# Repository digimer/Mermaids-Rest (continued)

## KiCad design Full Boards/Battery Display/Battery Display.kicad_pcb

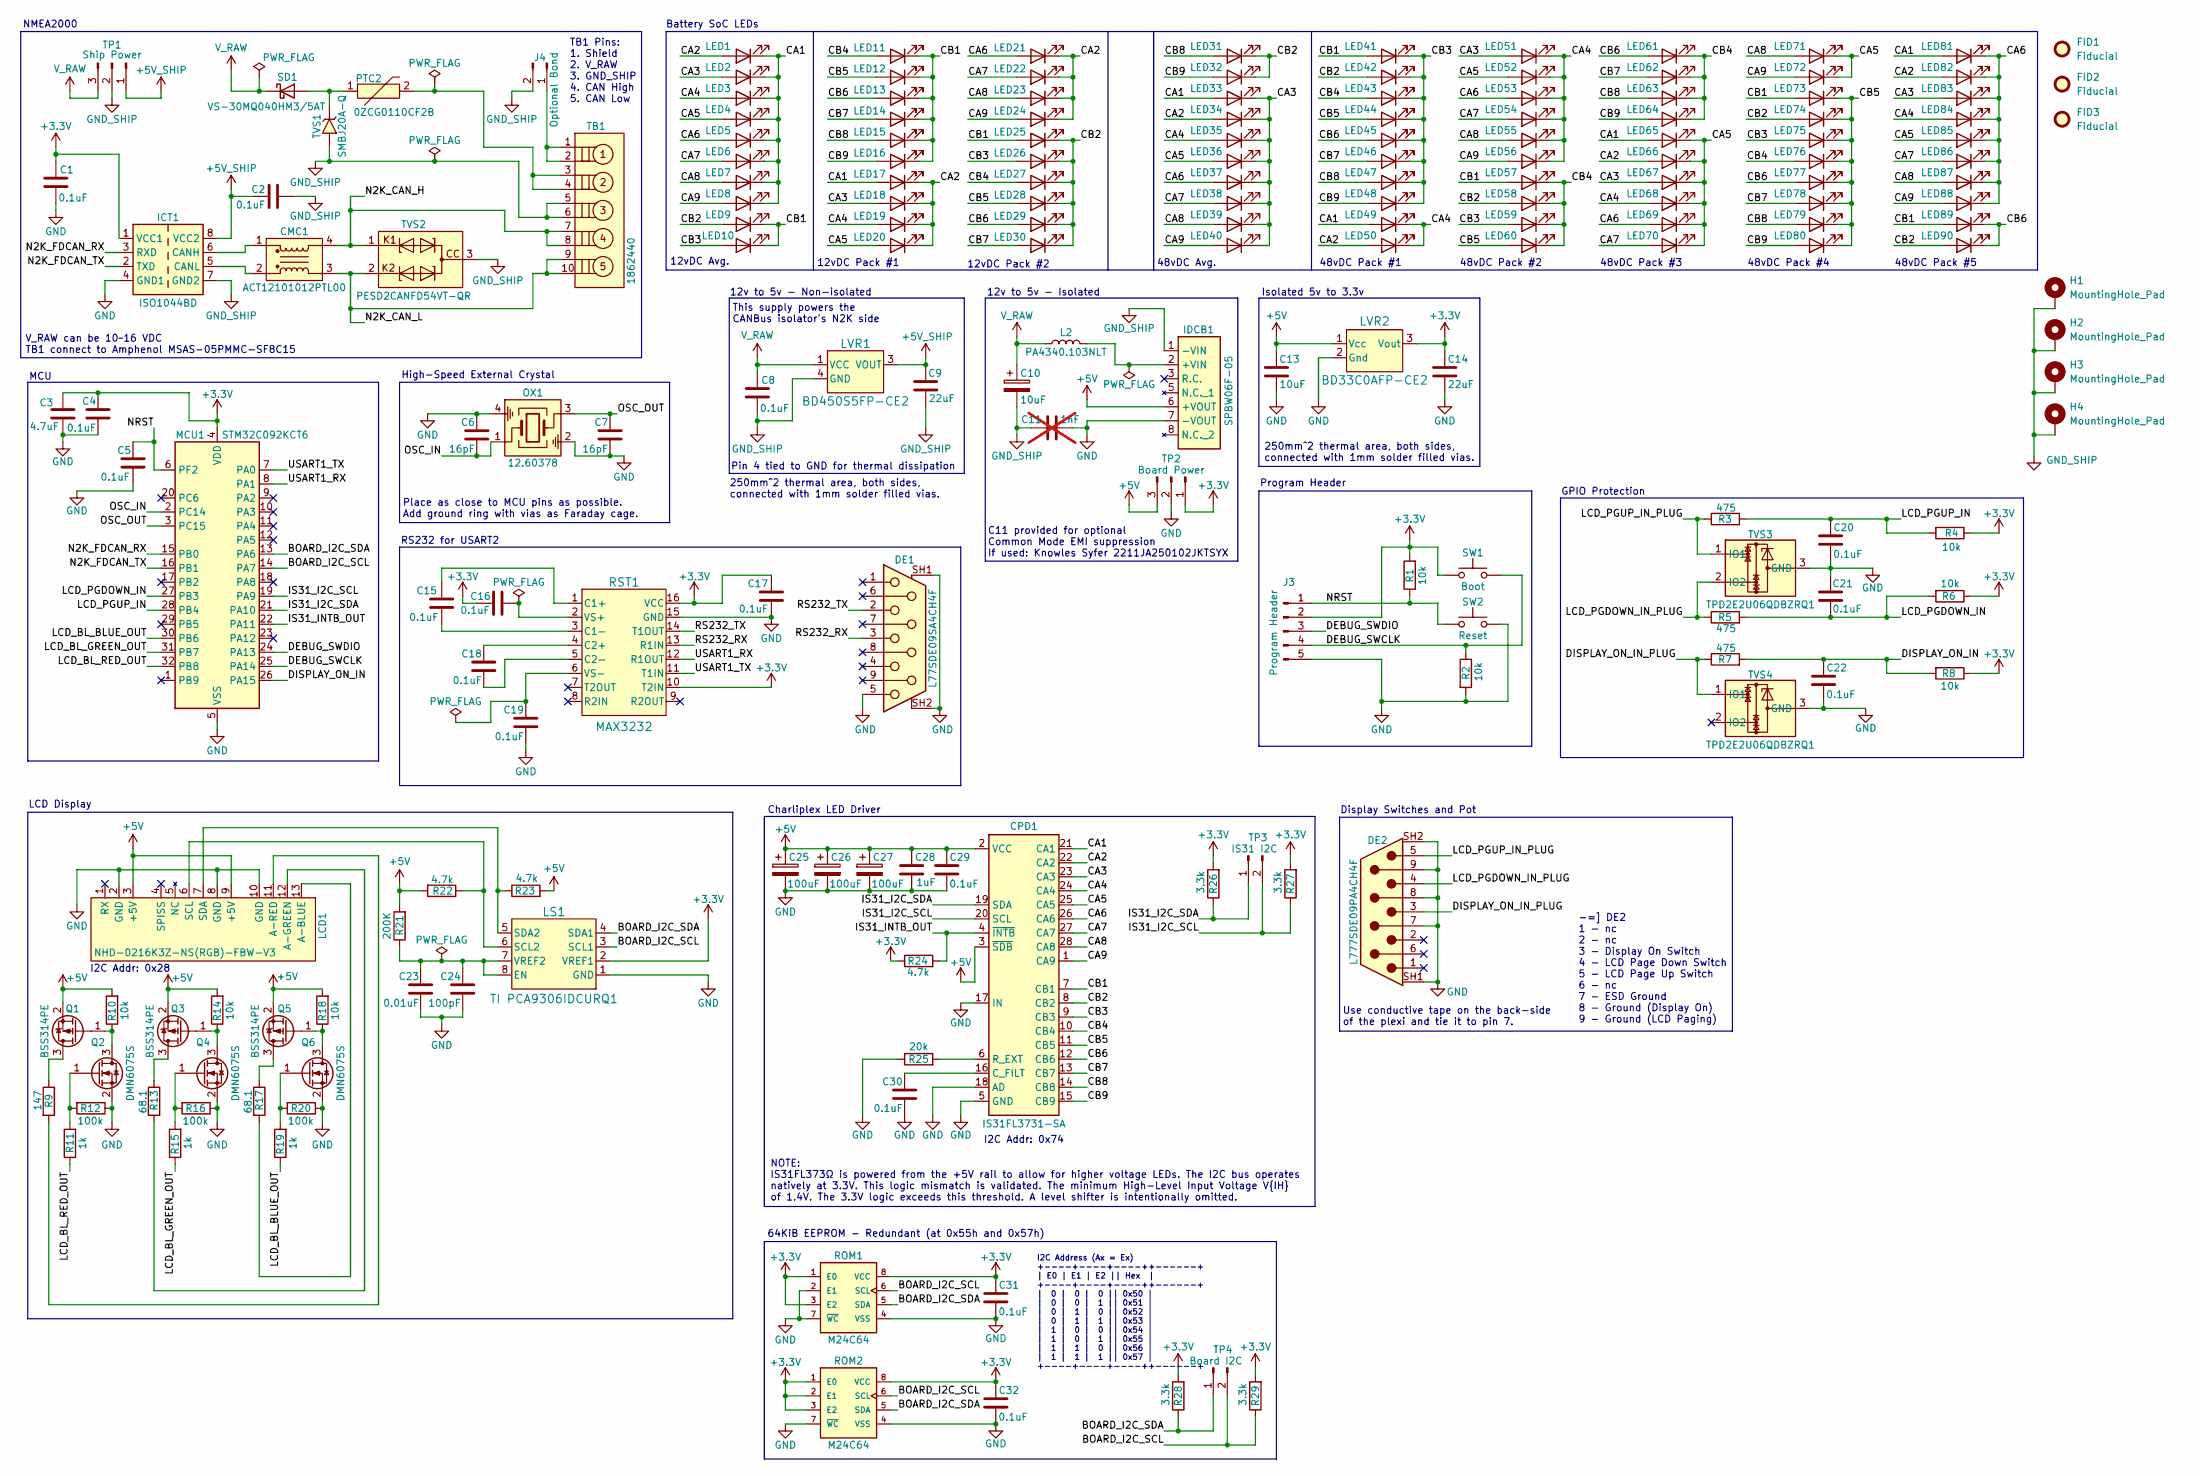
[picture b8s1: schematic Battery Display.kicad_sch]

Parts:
C1, C2, C4, C5, C8, C15, C16, C17, C18, C19, C20, C21, C22, C29, C30, C31, C32: 0.1uF; Kyocera AVX 0805; Part Kyocera 08051C104K4Z2A
C3: 4.7uF; Kyocera AVX 1206; Part Kyocera 12065C475K4Z2A
C6, C7: 16pF; Kemet C0603X; Part Kemet C0603X160J5GACAUTO
C9, C14: 22uF; Murata GCJ31CR71A; Part Murata GCJ31CR71A226KE01L
C10: 10uF; Kyocera AVX 1206; Part Kyocera 12105C106K4Z2A
C11: 1nF; Knowles Syfer 2211JA25; Part Knowles Syfer 2211JA250102JKTSYX; not fitted
C13: 10uF; TDK CGA5; Part TDK CGA5L1X7R1E106K160DC
C23: 0.01uF; Kemet C0805X; Part Kemet FA18NP01H103JNU06
C24: 100pF; Kemet C0805X; Part Kemet C0805X101J5GACAUTO
C25, C26, C27: 100uF; CP_Radial_D8.0mm_P3.50mm; Part Kemet A7C0KS107M1HAAS031
C28: 1uF; Kemet C1206C; Part Kemet C1206X105J1RACAUTO
CMC1: ACT12101012PTL00; TDK ACT12101012PTL00; Part TDK ACT12101012PTL00
CPD1: IS31FL3731-SA; SSOP-28_5.3x10.2mm_P0.65mm; Part Lumissil IS31FL3731-SALS2-TR
DE1: L77SDE09SA4CH4F; Amphenol_L77SDE09SA4CH4F; Part Amphenol L77SDE09SA4CH4F
DE2: L777SDE09PA4CH4F; Amphenol L777SDE09PA4CH4F; Part AAmphenol L777SDE09PA4CH4F
FID1, FID2, FID3: Fiducial; Fiducial_0.5mm_Mask1.5mm
H1, H2, H3, H4: MountingHole_Pad; MountingHole_4mm_Pad_Via
ICT1: ISO1044BD; TI ISO1044BDR; Part TI ISO1044BDR
IDCB1: SPBW06F-05; Meanwell SPBW06F05; Part Meanwell SPBW06F-05
J3: Program Header; PinHeader_1x05_P2.54mm_Horizontal
J4: Optional Bond; PinHeader_1x02_P2.54mm_Vertical
L2: PA4340.103NLT; Pulse PA4340.103NLT; Part Pulse PA4340.103NLT
LCD1: NHD-0216K3Z-NS(RGB)-FBW-V3; Newhaven Display NHD-0216K3Z-NS(RGB)-FBW-V3; Part Newhaven Display NHD-0216K3Z-NS(RGB)-FB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
LED1, LED2, LED3, LED4, LED5, LED6, LED7, LED8, LED9, LED10, LED11, LED12, LED13, LED14, LED15, LED16, LED17, LED18, LED19, LED20, LED21, LED22, LED23, LED24, LED25, LED26, LED27, LED28, LED29, LED30, LED31, LED32, LED33, LED34, LED35, LED36, LED37, LED38, LED39, LED40, LED41, LED42, LED43, LED44, LED45, LED46, LED47, LED48, LED49, LED50, LED51, LED52, LED53, LED54, LED55, LED56, LED57, LED58, LED59, LED60, LED61, LED62, LED63, LED64, LED65, LED66, LED67, LED68, LED69, LED70, LED71, LED72, LED73, LED74, LED75, LED76, LED77, LED78, LED79, LED80, LED81, LED82, LED83, LED84, LED85, LED86, LED87, LED88, LED89, LED90: LED; Kingbright WP383SURDTK; Part Kingbright WP383SURDTK
LS1: TI PCA9306IDCURQ1; TI PCA9306; Part Texas Instruments PCA9306IDCURQ1
LVR1: BD450S5FP-CE2; Rohm BD4xxS5 TO252-3; Part Rohm BD450S5FP-CE2
LVR2: BD33C0AFP-CE2; Rohm BD33C0; Part Rohm BD33C0AFP-CE2
MCU1: STM32C092KCT6; STM STM32C0 LQFP-32; Part STM STM32C092KCT6
OX1: 12.60378; Crystal_SMD_3225-4Pin_3.2x2.5mm; Part Geyer 12.60378
PTC2: 0ZCG0110CF2B; Bel Fuse 0ZCG; Part Bel Fuse 0ZCG0110CF2B
Q1, Q3, Q5: BSS314PE; SOT-23; Part Infineon BSS314PEH6327XTSA1
Q2, Q4, Q6: DMN6075S; SOT-23; Part Diodes Inc DMN6075SQ-7
R1, R2, R4, R6, R8, R10, R14, R18: 10k; Stackpole RMCA0805; Part Stackpole RMCA0805FT10K0-HP
R3, R5, R7: 475; Stackpole RNCP0805; Part Stackpole RNCP0805FTD475R
R9: 147; Stackpole RNCP0805; Part Stackpole RNCP0805FTD150R
R11, R15, R19: 1k; Stackpole RNCP0805; Part Stackpole RNCP0805FTD1K00
R12, R16, R20: 100k; Stackpole RMCA0805; Part Stackpole RMCA0805FT100K-HP
R13, R17: 68.1; Stackpole RNCP0805; Part Stackpole RNCP0805FTD68R1
R21: 200K; Yageo AE0805; Part Yageo RNCP0805FTD475R
R22, R23, R24: 4.7k; Stackpole RMCA0805; Part Stackpole RMCA0805FT4K70-HP
R25: 20k; Stackpole RMCA0805; Part Stackpole RMCA0805FT20K0-HP
R26, R27, R28, R29: 3.3k; Stackpole RNCF0805; Part Stackpole RNCF0805DTE3K30
ROM1, ROM2: M24C64; STM M24C64-RMN6P; Part STM M24C64-RMN6P
RST1: MAX3232; TI MAX3232EIPWRQ1; Part TI MAX3232EIPWRQ1
SD1: VS-30MQ040HM3/5AT; D_SMA; Part Vishay VS-30MQ040HM3/5AT
SW1: Boot; Same Sky TS03-66; Part Same Sky TS03-66-50-BK-160-LCR-D-67
SW2: Reset; Same Sky TS03-66; Part Same Sky TS03-66-50-BK-160-LCR-D-67
TB1: 1862440; Phoenix Contact 1862440; Part Phoenix Contact 1862440
TP1: Ship Power; PinHeader_1x03_P2.54mm_Vertical
TP2: Board Power; PinHeader_1x03_P2.54mm_Vertical
TP3: IS31 I2C; PinHeader_1x02_P2.54mm_Vertical
TP4: Board I2C; PinHeader_1x02_P2.54mm_Vertical
TVS1: SMBJ20A-Q; Bourns SMBJ20; Part Bourns SMBJ20A-Q
TVS2: PESD2CANFD54VT-QR; Nexperia PESD2CANFD; Part Nexperia PESD2CANFD54VT-QR
TVS3, TVS4: TPD2E2U06QDBZRQ1; TI TPD2E2U06; Part TI TPD2E2U06QDBZRQ1

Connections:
+3.3V: C1.2, C3.1, C4.2, C14.2, C16.2, C17.2, C31.2, C32.2, ICT1.1 (VCC1), J3.2, LS1.2 (VREF1), LVR2.3 (Vout), MCU1.4 (VDD), R1.2, R4.1, R6.1, R8.1, R24.1, R26.2, R27.2, R28.2, R29.2, ROM1.1 (E0), ROM1.3 (E2), ROM1.8 (VCC), ROM2.1 (E0), ROM2.2 (E1), ROM2.3 (E2), ROM2.8 (VCC), RST1.10 (T2IN), RST1.16 (VCC), SW1.1 (A), SW1.2 (A), TP2.1
+5V: C13.2, C25.1, C26.1, C27.1, C28.1, C29.2, CPD1.2 (VCC), CPD1.3 (~SDB), IDCB1.6 (+VOUT), LCD1.3 (+5V), LCD1.9 (+5V), LVR2.1 (Vcc), Q1.2 (S), Q3.2 (S), Q5.2 (S), R10.2, R14.2, R18.2, R21.2, R22.2, R23.2, TP2.3
+5V_SHIP: C2.2, C9.2, ICT1.8 (VCC2), LVR1.3 (VOUT), TP1.1
/BOARD_I2C_SCL: LS1.3 (SCL1), MCU1.14 (PA7), R29.1, ROM1.6 (SCL), ROM2.6 (SCL), TP4.2
/BOARD_I2C_SDA: LS1.4 (SDA1), MCU1.13 (PA6), R28.1, ROM1.5 (SDA), ROM2.5 (SDA), TP4.1
/CA1: CPD1.21 (CA1), LED1.1 (K), LED2.1 (K), LED3.1 (K), LED4.1 (K), LED5.1 (K), LED6.1 (K), LED7.1 (K), LED8.1 (K), LED17.2 (A), LED33.2 (A), LED49.2 (A), LED65.2 (A), LED81.2 (A)
/CA2: CPD1.22 (CA2), LED1.2 (A), LED17.1 (K), LED18.1 (K), LED19.1 (K), LED20.1 (K), LED21.1 (K), LED22.1 (K), LED23.1 (K), LED24.1 (K), LED34.2 (A), LED50.2 (A), LED66.2 (A), LED82.2 (A)
/CA3: CPD1.23 (CA3), LED2.2 (A), LED18.2 (A), LED33.1 (K), LED34.1 (K), LED35.1 (K), LED36.1 (K), LED37.1 (K), LED38.1 (K), LED39.1 (K), LED40.1 (K), LED51.2 (A), LED67.2 (A), LED83.2 (A)
/CA4: CPD1.24 (CA4), LED3.2 (A), LED19.2 (A), LED35.2 (A), LED49.1 (K), LED50.1 (K), LED51.1 (K), LED52.1 (K), LED53.1 (K), LED54.1 (K), LED55.1 (K), LED56.1 (K), LED68.2 (A), LED84.2 (A)
/CA5: CPD1.25 (CA5), LED4.2 (A), LED20.2 (A), LED36.2 (A), LED52.2 (A), LED65.1 (K), LED66.1 (K), LED67.1 (K), LED68.1 (K), LED69.1 (K), LED70.1 (K), LED71.1 (K), LED72.1 (K), LED85.2 (A)
/CA6: CPD1.26 (CA6), LED5.2 (A), LED21.2 (A), LED37.2 (A), LED53.2 (A), LED69.2 (A), LED81.1 (K), LED82.1 (K), LED83.1 (K), LED84.1 (K), LED85.1 (K), LED86.1 (K), LED87.1 (K), LED88.1 (K)
/CA7: CPD1.27 (CA7), LED6.2 (A), LED22.2 (A), LED38.2 (A), LED54.2 (A), LED70.2 (A), LED86.2 (A)
/CA8: CPD1.28 (CA8), LED7.2 (A), LED23.2 (A), LED39.2 (A), LED55.2 (A), LED71.2 (A), LED87.2 (A)
/CA9: CPD1.1 (CA9), LED8.2 (A), LED24.2 (A), LED40.2 (A), LED56.2 (A), LED72.2 (A), LED88.2 (A)
/CB1: CPD1.7 (CB1), LED9.1 (K), LED10.1 (K), LED11.1 (K), LED12.1 (K), LED13.1 (K), LED14.1 (K), LED15.1 (K), LED16.1 (K), LED25.2 (A), LED41.2 (A), LED57.2 (A), LED73.2 (A), LED89.2 (A)
/CB2: CPD1.8 (CB2), LED9.2 (A), LED25.1 (K), LED26.1 (K), LED27.1 (K), LED28.1 (K), LED29.1 (K), LED30.1 (K), LED31.1 (K), LED32.1 (K), LED42.2 (A), LED58.2 (A), LED74.2 (A), LED90.2 (A)
/CB3: CPD1.9 (CB3), LED10.2 (A), LED26.2 (A), LED41.1 (K), LED42.1 (K), LED43.1 (K), LED44.1 (K), LED45.1 (K), LED46.1 (K), LED47.1 (K), LED48.1 (K), LED59.2 (A), LED75.2 (A)
/CB4: CPD1.10 (CB4), LED11.2 (A), LED27.2 (A), LED43.2 (A), LED57.1 (K), LED58.1 (K), LED59.1 (K), LED60.1 (K), LED61.1 (K), LED62.1 (K), LED63.1 (K), LED64.1 (K), LED76.2 (A)
/CB5: CPD1.11 (CB5), LED12.2 (A), LED28.2 (A), LED44.2 (A), LED60.2 (A), LED73.1 (K), LED74.1 (K), LED75.1 (K), LED76.1 (K), LED77.1 (K), LED78.1 (K), LED79.1 (K), LED80.1 (K)
/CB6: CPD1.12 (CB6), LED13.2 (A), LED29.2 (A), LED45.2 (A), LED61.2 (A), LED77.2 (A), LED89.1 (K), LED90.1 (K)
/CB7: CPD1.13 (CB7), LED14.2 (A), LED30.2 (A), LED46.2 (A), LED62.2 (A), LED78.2 (A)
/CB8: CPD1.14 (CB8), LED15.2 (A), LED31.2 (A), LED47.2 (A), LED63.2 (A), LED79.2 (A)
/CB9: CPD1.15 (CB9), LED16.2 (A), LED32.2 (A), LED48.2 (A), LED64.2 (A), LED80.2 (A)
/DEBUG_SWCLK: J3.4, MCU1.25 (PA14), R2.1, SW1.3 (B), SW1.4 (B)
/DEBUG_SWDIO: J3.3, MCU1.24 (PA13)
/DISPLAY_ON_IN: C22.2, MCU1.26 (PA15), R7.2, R8.2
/DISPLAY_ON_IN_PLUG: DE2.3, R7.1, TVS4.1 (IO1)
/IS31_I2C_SCL: CPD1.20 (SCL), MCU1.19 (PA9), R27.1, TP3.2
/IS31_I2C_SDA: CPD1.19 (SDA), MCU1.21 (PA10), R26.1, TP3.1
/IS31_INTB_OUT: CPD1.4 (~INTB), MCU1.22 (PA11), R24.2
/LCD_BL_BLUE_OUT: MCU1.30 (PB6), R19.1
/LCD_BL_GREEN_OUT: MCU1.31 (PB7), R15.1
/LCD_BL_RED_OUT: MCU1.32 (PB8), R11.1
/LCD_PGDOWN_IN: C21.2, MCU1.27 (PB3), R5.2, R6.2
/LCD_PGDOWN_IN_PLUG: DE2.4, R5.1, TVS3.2 (IO2)
/LCD_PGUP_IN: C20.2, MCU1.28 (PB4), R3.2, R4.2
/LCD_PGUP_IN_PLUG: DE2.5, R3.1, TVS3.1 (IO1)
/N2K_CAN_H: CMC1.4 (O1), TB1.7, TB1.8, TVS2.1
/N2K_CAN_L: CMC1.3 (O2), TB1.9, TB1.10, TVS2.2
/N2K_FDCAN_RX: ICT1.3 (RXD), MCU1.15 (PB0)
/N2K_FDCAN_TX: ICT1.2 (TXD), MCU1.16 (PB1)
/NRST: C5.2, J3.1, MCU1.6 (PF2), R1.1, SW2.1 (A), SW2.2 (A)
/OSC_IN: C6.1, MCU1.2 (PC14), OX1.1
/OSC_OUT: C7.2, MCU1.3 (PC15), OX1.3
/RS232_RX: DE1.3, RST1.13 (R1IN)
/RS232_TX: DE1.2, RST1.14 (T1OUT)
/USART1_RX: MCU1.8 (PA1), RST1.12 (R1OUT)
/USART1_TX: MCU1.7 (PA0), RST1.11 (T1IN)
GND: C1.1, C3.2, C4.1, C5.1, C6.2, C7.1, C11.2, C13.1, C14.1, C17.1, C19.1, C20.1, C21.1, C22.1, C23.1, C24.1, C25.2, C26.2, C27.2, C28.2, C29.1, C30.1, C31.1, C32.1, CPD1.5 (GND), CPD1.17 (IN), CPD1.18 (AD), DE1.5, DE1.SH1, DE1.SH2, DE2.7, DE2.8, DE2.9, DE2.SH1, DE2.SH2, ICT1.4 (GND1), IDCB1.7 (-VOUT), J3.5, LCD1.2 (GND), LCD1.8 (GND), LCD1.10 (GND), LS1.1 (GND), LVR2.2 (Gnd), MCU1.5 (VSS), OX1.2, OX1.4, Q2.2 (S), Q4.2 (S), Q6.2 (S), R2.2, R12.1, R16.1, R20.1, R25.1, ROM1.2 (E1), ROM1.4 (VSS), ROM1.7 (~WC), ROM2.4 (VSS), ROM2.7 (~WC), RST1.15 (GND), SW2.3 (B), SW2.4 (B), TP2.2, TVS3.3 (GND), TVS4.3 (GND)
GND_SHIP: C2.1, C8.1, C9.1, C10.2, C11.1, H1.1 (1_1), H2.1 (1_1), H3.1 (1_1), H4.1 (1_1), ICT1.7 (GND2), IDCB1.1 (-VIN), J4.2, LVR1.4 (GND), TB1.5, TB1.6, TP1.2, TVS1.2 (A), TVS2.3
unnamed: CMC1.1 (I1), ICT1.6 (CANH)
unnamed: CMC1.2 (I2), ICT1.5 (CANL)
unnamed: C30.2, CPD1.16 (C_FILT)
unnamed: CPD1.6 (R_EXT), R25.2
unnamed: IDCB1.2 (+VIN), L2.2
unnamed: J4.1, TB1.1, TB1.2
unnamed: LCD1.13 (A-BLUE), R17.2
unnamed: LCD1.12 (A-GREEN), R13.2
unnamed: LCD1.11 (A-RED), R9.2
unnamed: LCD1.6 (SCL), LS1.6 (SCL2), R22.1
unnamed: LCD1.7 (SDA), LS1.5 (SDA2), R23.1
unnamed: C23.2, C24.2, LS1.7 (VREF2), LS1.8 (EN), R21.1
unnamed: PTC2.2, TB1.3, TB1.4
unnamed: Q1.3 (D), R9.1
unnamed: Q1.1 (G), Q2.3 (D), R10.1
unnamed: Q2.1 (G), R11.2, R12.2
unnamed: Q3.3 (D), R13.1
unnamed: Q3.1 (G), Q4.3 (D), R14.1
unnamed: Q4.1 (G), R15.2, R16.2
unnamed: Q5.3 (D), R17.1
unnamed: Q5.1 (G), Q6.3 (D), R18.1
unnamed: Q6.1 (G), R19.2, R20.2
unnamed: C15.2, RST1.1 (C1+)
unnamed: C15.1, RST1.3 (C1-)
unnamed: C18.2, RST1.4 (C2+)
unnamed: C18.1, RST1.5 (C2-)
unnamed: C16.1, RST1.2 (VS+)
unnamed: C19.2, RST1.6 (VS-)
unnamed: PTC2.1, SD1.2 (A), TVS1.1 (K)
V_RAW: C8.2, C10.1, L2.1, LVR1.1 (VCC), SD1.1 (K), TP1.3

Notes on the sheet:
Battery SoC LEDs
250mm^2 thermal area, both sides, connected with 1mm solder filled vias.
NMEA2000
NOTE: IS31FL373Ω is powered from the +5V rail to allow for higher voltage LEDs. The I2C bus operates natively at 3.3V. This logic mismatch is validated. The minimum High-Level Input Voltage V{IH} of 1.4V. The 3.3V logic exceeds this threshold. A level shifter is intentionally omitted.
Charliplex LED Driver
48vDC Pack #2
48vDC Pack #3
C11 provided for optional Common Mode EMI suppression If used: Knowles Syfer 2211JA250102JKTSYX
48vDC Pack #4
LCD Display
MCU
-=] DE2 1 - nc 2 - nc 3 - Display On Switch 4 - LCD Page Down Switch 5 - LCD Page Up Switch 6 - nc 7 - ESD Ground 8 - Ground (Display On) 9 - Ground (LCD Paging)
Pin 4 tied to GND for thermal dissipation
48vDC Avg.
Program Header
Use conductive tape on the back-side of the plexi and tie it to pin 7.
12v to 5v - Isolated
12vDC Pack #1
12vDC Pack #2
Place as close to MCU pins as possible. Add ground ring with vias as Faraday cage.
High-Speed External Crystal
64KiB EEPROM - Redundant (at 0x55h and 0x57h)
12vDC Avg.
I2C Addr: 0x74
TB1 Pins: 1. Shield 2. V_RAW 3. GND_SHIP 4. CAN High 5. CAN Low
This supply powers the CANBus isolator's N2K side
I2C Address (Ax = Ex) +----+----+----++------+ | E0 | E1 | E2 || Hex | +----+----+----++------+ | 0 | 0 | 0 || 0x50 | | 0 | 0 | 1 || 0x51 | | 0 | 1 | 0 || 0x52 | | 0 | 1 | 1 || 0x53 | | 1 | 0 | 0 || 0x54 | | 1 | 0 | 1 || 0x55 | | 1 | 1 | 0 || 0x56 | | 1 | 1 | 1 || 0x57 | +----+----+----++------+
Isolated 5v to 3.3v
Display Switches and Pot
RS232 for USART2
I2C Addr: 0x28
48vDC Pack #5
V_RAW can be 10~16 VDC TB1 connect to Amphenol MSAS-05PMMC-SF8C15
GPIO Protection
12v to 5v - Non-isolated
48vDC Pack #1

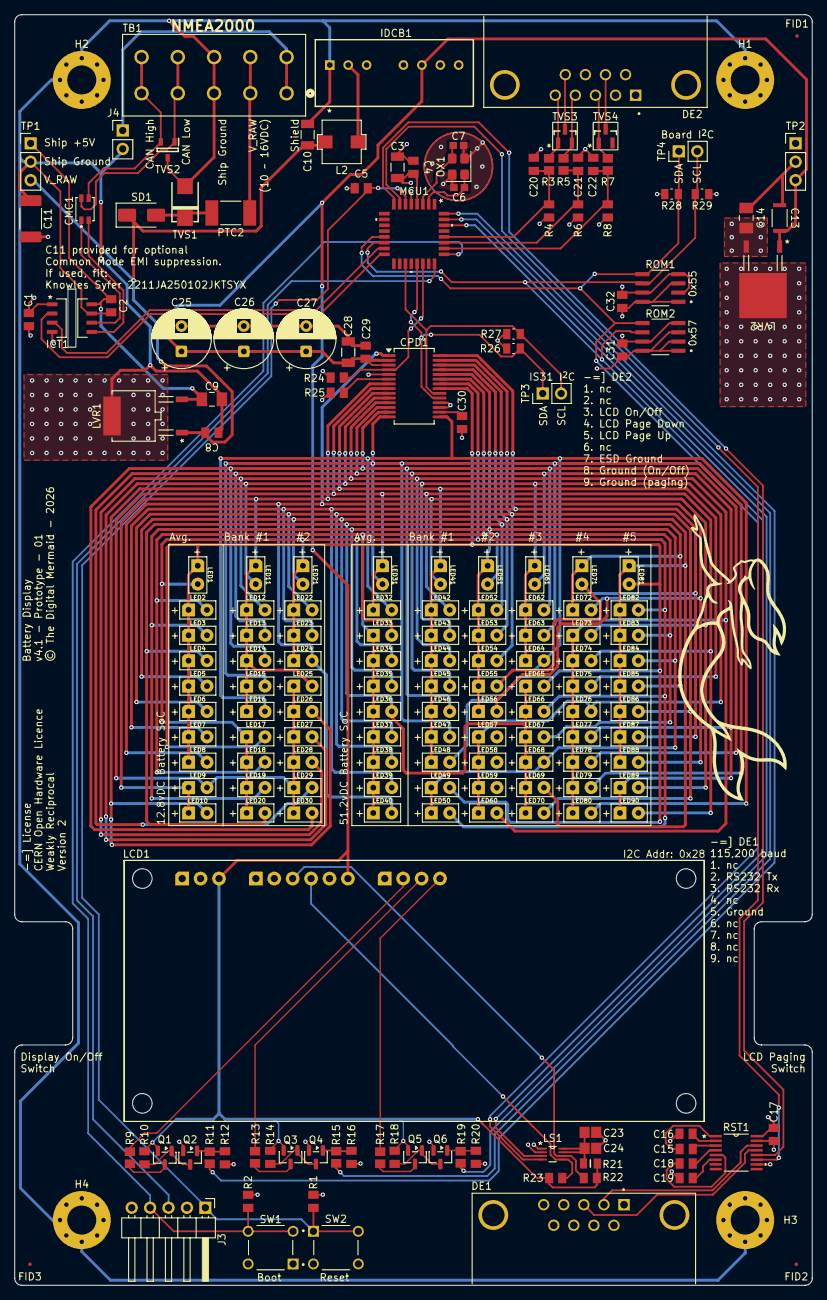
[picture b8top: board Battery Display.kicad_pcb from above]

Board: 4 copper layers, 110.0 x 175.2 mm, 195 parts (0 on the bottom side), 80 nets.

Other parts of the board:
TDM***: LOGO; Mermaid Silkscreen - 15mm

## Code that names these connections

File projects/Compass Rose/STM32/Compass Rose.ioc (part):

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Mcu.Name=STM32C092KCTx
Mcu.Package=LQFP32
Mcu.UserName=STM32C092KCTx
PA0.Signal=USART1_TX
PA1.Signal=USART1_RX
PA10.GPIOParameters=GPIO_Label
PA10.GPIO_Label=IS31_I2C_SDA
PA10.Signal=I2C1_SDA
PA11\ [PA9].GPIOParameters=GPIO_Label
PA11\ [PA9].GPIO_Label=IS31_INTB_OUT
PA11\ [PA9].Signal=GPIO_Output
PA13.Mode=Serial_Wire
PA13.Signal=DEBUG_SWDIO
PA14-BOOT0.Mode=Serial_Wire
PA14-BOOT0.Signal=DEBUG_SWCLK
PA15.GPIOParameters=GPIO_Label
PA15.GPIO_Label=DISPLAY_ON_IN
PA15.Signal=GPIO_Input
PA2.GPIOParameters=GPIO_Label
PA2.GPIO_Label=CONFIG1_IN
PA2.Signal=GPIO_Input
PA3.GPIOParameters=GPIO_Label
PA3.GPIO_Label=CONFIG2_IN
PA3.Signal=GPIO_Input
PA6.GPIOParameters=GPIO_Label
PA6.GPIO_Label=BOARD_I2C_SDA
PA6.Mode=I2C
PA6.Signal=I2C2_SDA
PA7.GPIOParameters=GPIO_Label
PA7.GPIO_Label=BOARD_I2C_SCL
PA7.Mode=I2C
PA7.Signal=I2C2_SCL
PA9.GPIOParameters=GPIO_Label
PA9.GPIO_Label=IS31_I2C_SCL
PA9.Signal=I2C1_SCL
PB0.GPIOParameters=GPIO_Label
PB0.GPIO_Label=N2K_FDCAN_RX
PB0.Mode=FDCAN_Activate
PB0.Signal=FDCAN1_RX
PB1.GPIOParameters=GPIO_Label
PB1.GPIO_Label=N2K_FDCAN_TX
PB1.Mode=FDCAN_Activate
PB1.Signal=FDCAN1_TX
PB3.GPIOParameters=GPIO_Label
PB3.GPIO_Label=LCD_PGDOWN_IN
PB3.Signal=GPIO_Input
PB4.GPIOParameters=GPIO_Label
PB4.GPIO_Label=LCD_PGUP_IN
PB4.Signal=GPIO_Input
PB6.GPIOParameters=GPIO_Label
PB6.GPIO_Label=LCD_BL_BLUE_OUT
PB6.Signal=GPIO_Output
PB7.GPIOParameters=GPIO_Label
PB7.GPIO_Label=LCD_BL_GREEN_OUT
PB7.Signal=GPIO_Output
PB8.GPIOParameters=GPIO_Label
PB8.GPIO_Label=LCD_BL_RED_OUT
PB8.Signal=GPIO_Output
PC14-OSCX_IN(PC14).GPIOParameters=GPIO_Label
PC14-OSCX_IN(PC14).GPIO_Label=OSC_IN
PC14-OSCX_IN(PC14).Signal=RCC_OSCX_IN
PC15-OSCX_OUT(PC15).GPIOParameters=GPIO_Label
PC15-OSCX_OUT(PC15).GPIO_Label=OSC_OUT
PC15-OSCX_OUT(PC15).Signal=RCC_OSCX_OUT
PF2-NRST.GPIOParameters=GPIO_Label
PF2-NRST.GPIO_Label=NRST
PF2-NRST.Signal=GPIO_Output
RCC.HSE_VALUE=8000000
RCC.SYSCLKFreq_VALUE=12000000
board=custom

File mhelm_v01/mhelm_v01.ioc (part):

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Mcu.Name=STM32F030R8Tx
Mcu.Package=LQFP64
Mcu.UserName=STM32F030R8Tx
PA0.GPIOParameters=GPIO_Label
PA0.GPIO_Label=THROTTLE_STBD_POT
PA0.Mode=IN0
PA0.Signal=ADC_IN0
PA1.GPIOParameters=GPIO_Label
PA1.GPIO_Label=REGEN_POT
PA1.Mode=IN1
PA1.Signal=ADC_IN1
PA10.GPIOParameters=GPIO_Label
PA10.GPIO_Label=SPEED_HIGH_SW_OUT
PA10.Signal=GPIO_Output
PA11.GPIOParameters=GPIO_Label
PA11.GPIO_Label=SPEED_LOW_SW_OUT
PA11.Signal=GPIO_Output
PA13.GPIOParameters=GPIO_Label
PA13.GPIO_Label=TMS
PA13.Mode=Serial_Wire
PA13.Signal=SYS_SWDIO
PA14.GPIOParameters=GPIO_Label
PA14.GPIO_Label=TCK
PA14.Mode=Serial_Wire
PA14.Signal=SYS_SWCLK
PA2.GPIOParameters=GPIO_Speed,GPIO_PuPd,GPIO_Label,GPIO_Mode
PA2.GPIO_Label=USART_TX
PA2.GPIO_Mode=GPIO_MODE_AF_PP
PA2.GPIO_PuPd=GPIO_NOPULL
PA2.GPIO_Speed=GPIO_SPEED_FREQ_LOW
PA2.Mode=Asynchronous
PA2.Signal=USART2_TX
PA3.GPIOParameters=GPIO_Speed,GPIO_PuPd,GPIO_Label,GPIO_Mode
PA3.GPIO_Label=USART_RX
PA3.GPIO_Mode=GPIO_MODE_AF_PP
PA3.GPIO_PuPd=GPIO_NOPULL
PA3.GPIO_Speed=GPIO_SPEED_FREQ_LOW
PA3.Mode=Asynchronous
PA3.Signal=USART2_RX
PA4.GPIOParameters=GPIO_PuPd,GPIO_Label
PA4.GPIO_Label=MAIN_SW_IN
PA4.GPIO_PuPd=GPIO_PULLUP
PA4.Signal=GPIO_Input
PA5.GPIOParameters=GPIO_Speed,GPIO_PuPd,GPIO_Label,GPIO_Mode
PA5.GPIO_Label=LD2 [Green Led]
PA5.GPIO_Mode=GPIO_MODE_OUTPUT_PP
PA5.GPIO_PuPd=GPIO_NOPULL
PA5.GPIO_Speed=GPIO_SPEED_FREQ_LOW
PA5.Signal=GPIO_Output
PA6.GPIOParameters=GPIO_PuPd,GPIO_Label
PA6.GPIO_Label=THROTTLE_STOP_SW_IN
PA6.GPIO_PuPd=GPIO_PULLUP
PA6.Signal=GPIO_Input
PA7.GPIOParameters=GPIO_PuPd,GPIO_Label
PA7.GPIO_Label=SPEED_HIGH_SW_IN
PA7.GPIO_PuPd=GPIO_PULLUP
PA7.Signal=GPIO_Input
PA8.GPIOParameters=GPIO_PuPd,GPIO_Label
PA8.GPIO_Label=SPEED_LOW_SW_IN
PA8.GPIO_PuPd=GPIO_PULLUP
PA8.Signal=GPIO_Input
PA9.GPIOParameters=GPIO_Label
PA9.GPIO_Label=FOOT_SW_OUT
PA9.Signal=GPIO_Output
PB1.GPIOParameters=GPIO_PuPd,GPIO_Label
PB1.GPIO_Label=LCD1_SELECT_PREV
PB1.GPIO_PuPd=GPIO_PULLUP
PB1.Signal=GPIO_Input
PB10.GPIOParameters=GPIO_Label
PB10.GPIO_Label=LCD_SCL
PB10.Mode=I2C
PB10.Signal=I2C2_SCL
PB11.GPIOParameters=GPIO_Label
PB11.GPIO_Label=LCD_SDA
PB11.Mode=I2C
PB11.Signal=I2C2_SDA
PB13.GPIOParameters=GPIO_PuPd,GPIO_Label
PB13.GPIO_Label=THROTTLE_STBD_SELECT
PB13.GPIO_PuPd=GPIO_PULLUP
PB13.Signal=GPIO_Input
PB14.GPIOParameters=GPIO_PuPd,GPIO_Label
PB14.GPIO_Label=THROTTLE_PORT_SELECT
PB14.GPIO_PuPd=GPIO_PULLUP
PB14.Signal=GPIO_Input
PB2.GPIOParameters=GPIO_PuPd,GPIO_Label
PB2.GPIO_Label=LCD1_SELECT_NEXT
PB2.GPIO_PuPd=GPIO_PULLUP
PB2.Signal=GPIO_Input
PB6.GPIOParameters=GPIO_Label
PB6.GPIO_Label=DAC_SCL
PB6.Mode=I2C
PB6.Signal=I2C1_SCL
PB7.GPIOParameters=GPIO_Label
PB7.GPIO_Label=DAC_SDA
PB7.Mode=I2C
PB7.Signal=I2C1_SDA
PC0.GPIOParameters=GPIO_Label
PC0.GPIO_Label=DEBUG_0
PC0.Signal=GPIO_Output
PC1.GPIOParameters=GPIO_Label
PC1.GPIO_Label=DEBUG_1
PC1.Signal=GPIO_Output
PC13.GPIOParameters=GPIO_Label,GPIO_ModeDefaultEXTI
PC13.GPIO_Label=B1 [Blue PushButton]
PC13.GPIO_ModeDefaultEXTI=GPIO_MODE_IT_FALLING
PC13.Signal=GPXTI13
PC14-OSC32_IN.Mode=LSE-External-Oscillator
PC14-OSC32_IN.Signal=RCC_OSC32_IN
PC15-OSC32_OUT.Mode=LSE-External-Oscillator
PC15-OSC32_OUT.Signal=RCC_OSC32_OUT
PC3.GPIOParameters=GPIO_Label
PC3.GPIO_Label=THROTTLE_PORT_POT
PC3.Mode=IN13
PC3.Signal=ADC_IN13
PC6.GPIOParameters=GPIO_Label
PC6.GPIO_Label=LCD1_BL_RED
PC6.Signal=S_TIM3_CH1
PC7.GPIOParameters=GPIO_Label
PC7.GPIO_Label=LCD1_BL_GREEN
PC7.Signal=S_TIM3_CH2
PC8.GPIOParameters=GPIO_Label
PC8.GPIO_Label=LCD1_BL_BLUE
PC8.Signal=S_TIM3_CH3
PF0-OSC_IN.Mode=HSE-External-Clock-Source
PF0-OSC_IN.Signal=RCC_OSC_IN
PF1-OSC_OUT.Signal=RCC_OSC_OUT
RCC.SYSCLKFreq_VALUE=48000000
RCC.SYSCLKSource=RCC_SYSCLKSOURCE_PLLCLK
board=NUCLEO-F030R8
boardIOC=true

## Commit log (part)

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2024-08-25 Got the base of switch reading from SPI/DMA working.
    * Thanks to Triladar and Vbe!
2025-03-23 Added the basic light control tool
2025-08-03 First version of the (incomplete) switch control for avr
2025-08-03 Fixed inverted switch states
2025-11-03 Added KiCAD PCB files for the MCU, Relay Unit, Compass Rose and Battery Display boards.
2025-11-04 Updated PCBs to swap RVS diodes from SLD15-018 to SLD22-018. Also swapped out the inductor from 7847111100 to PA4340.103NLT.
2025-11-07 Updated boards and schematics.
    These are the version that have been ordered. Any further changes will be a new version.
